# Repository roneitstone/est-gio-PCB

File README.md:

# estagio-PCB
Bioimpedância
Arquivos relacionados ao projeto desenvolvido durante o estágio no laboratório de Instrumentação Biomédica da UFRJ.

--------------------------------------- english version ----------------------------------------------------------

Bioimpedance
Files related to the project developed during the internship at the Biomedical Instrumentation laboratory of UFRJ.

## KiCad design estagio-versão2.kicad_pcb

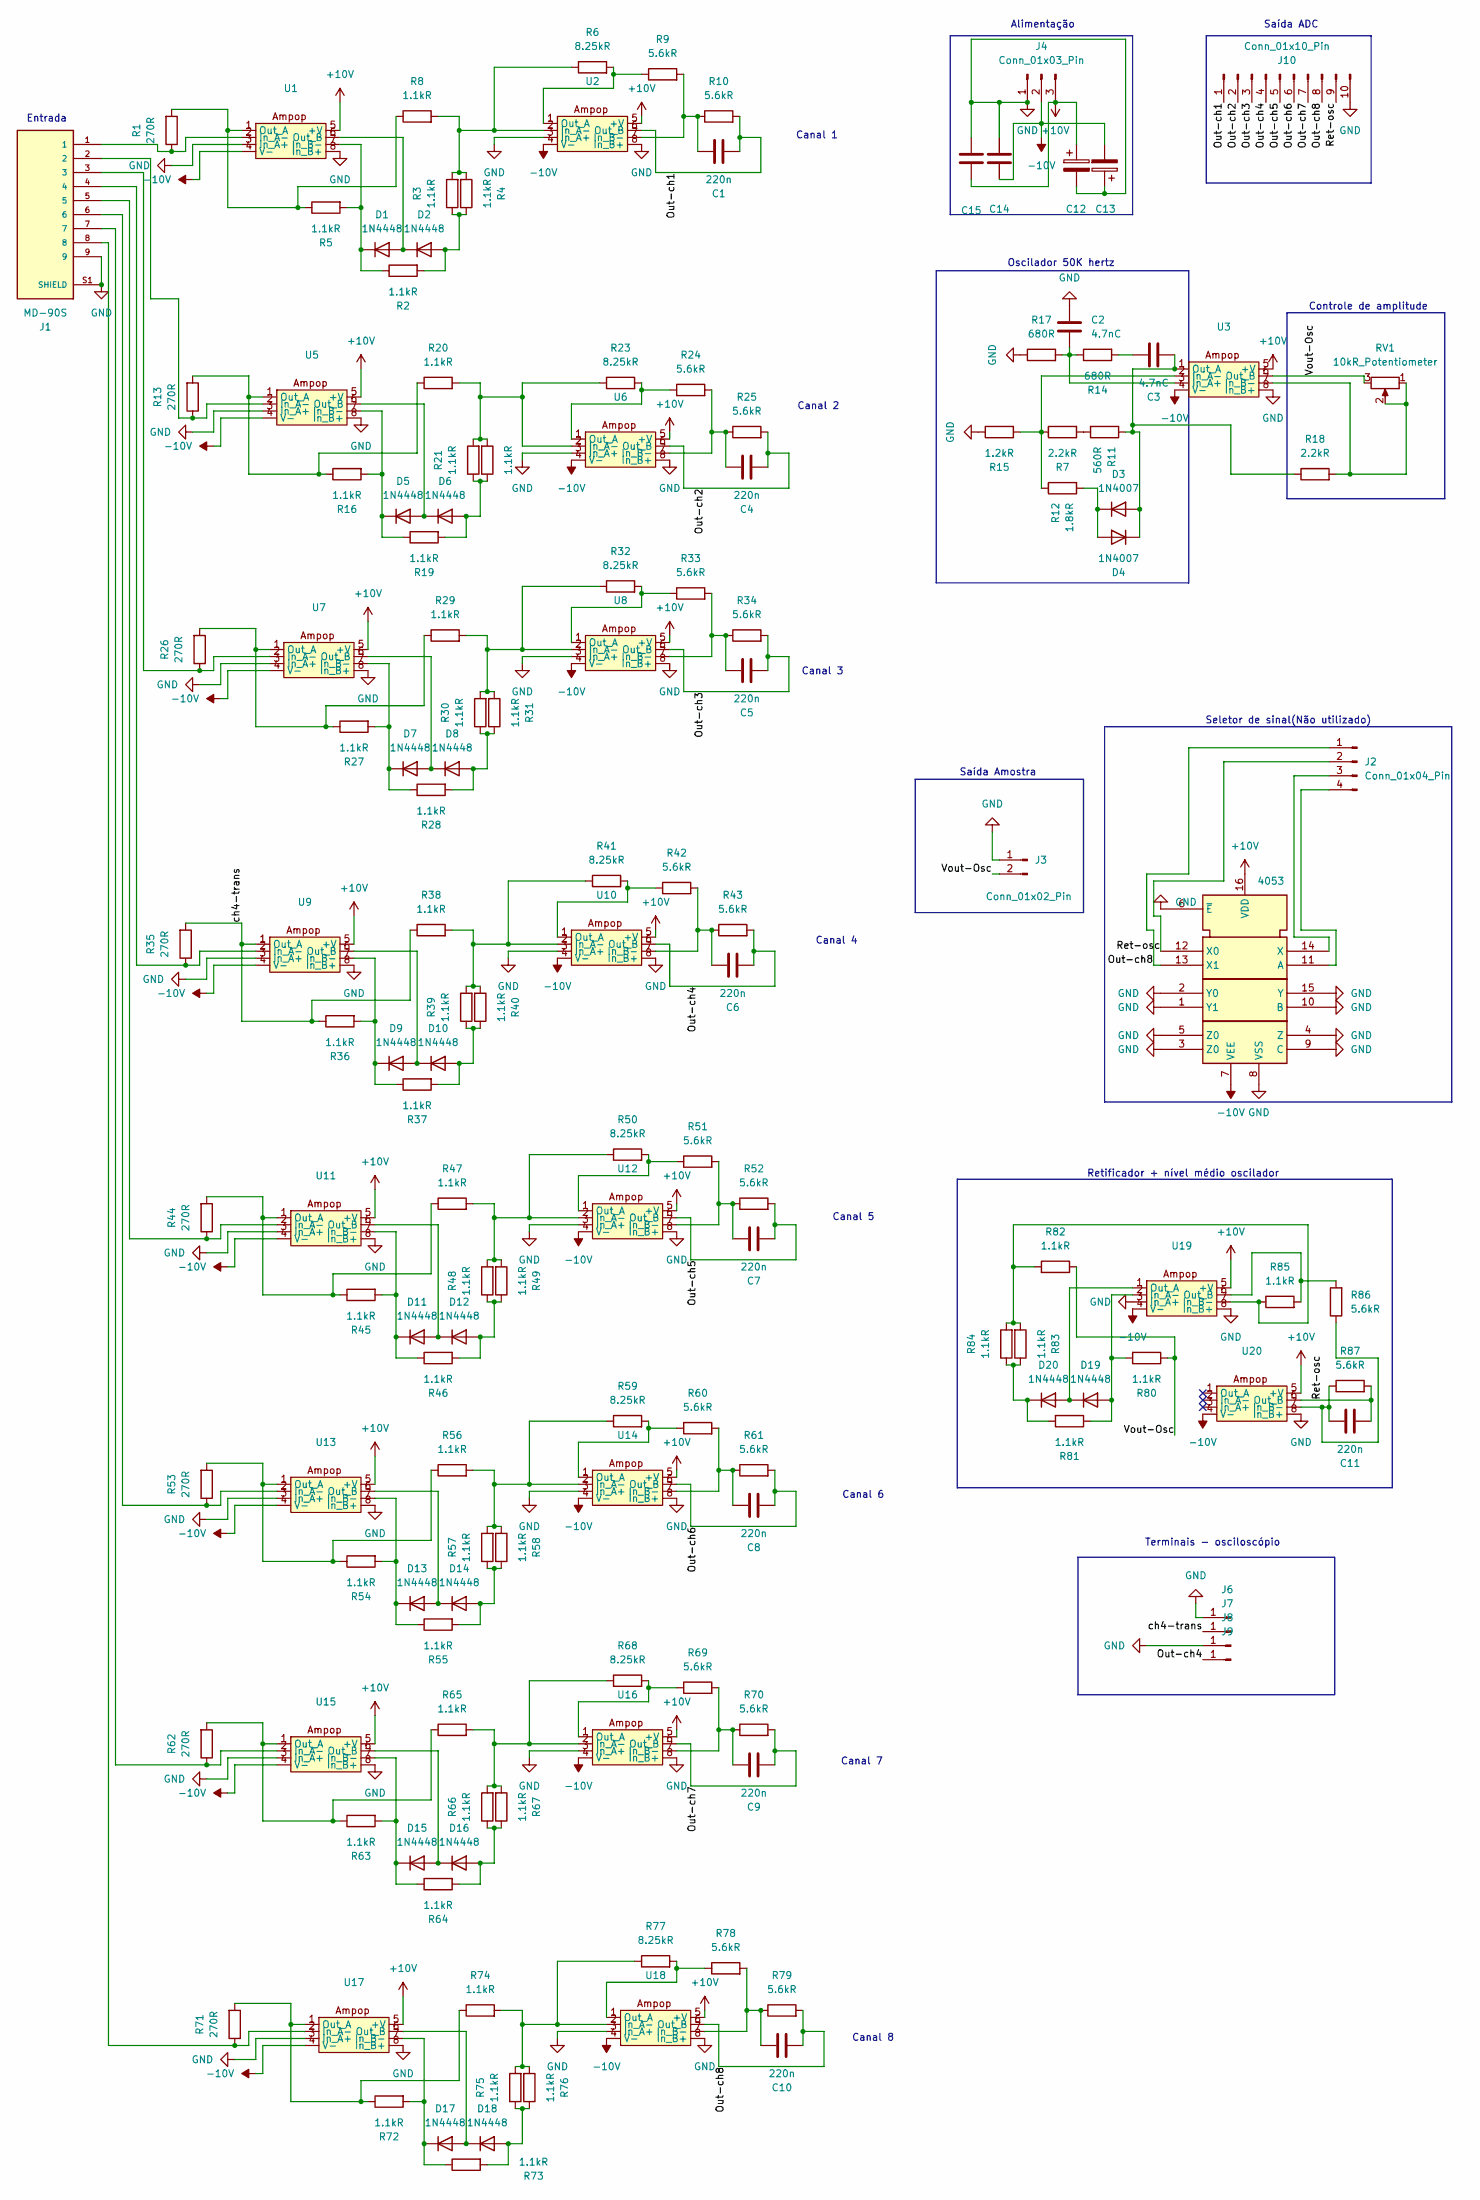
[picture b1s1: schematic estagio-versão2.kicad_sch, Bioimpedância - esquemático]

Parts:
C1, C4, C5, C6, C7, C8, C9, C10, C11: 220n; C_Rect_L7.2mm_W4.5mm_P5.00mm_FKS2_FKP2_MKS2_MKP2
C2, C3: 4.7nC; PinSocket_1x02_P2.54mm_Vertical
C12, C13: 1u; CP_Radial_D5.0mm_P2.50mm
C14, C15: 100n; C_Rect_L7.2mm_W4.5mm_P5.00mm_FKS2_FKP2_MKS2_MKP2
D1, D2, D5, D6, D7, D8, D9, D10, D11, D12, D13, D14, D15, D16, D17, D18, D19, D20: 1N4448; D_DO-35_SOD27_P7.62mm_Horizontal
D3, D4: 1N4007; D_DO-41_SOD81_P10.16mm_Horizontal
J1: MD-90S; CUI_MD-90S; PARTREV 02/18/2022
J2: Conn_01x04_Pin; PinHeader_1x04_P2.54mm_Vertical
J3: Conn_01x02_Pin; PinHeader_1x02_P2.54mm_Vertical
J4: Conn_01x03_Pin; JST_EH_B3B-EH-A_1x03_P2.50mm_Vertical
J6, J7, J8, J9: Conn_01x01_Pin; bullet
J10: Conn_01x10_Pin; PinHeader_1x10_P2.54mm_Vertical
R1, R13, R26, R35, R44, R53, R62, R71: 270R; YAG_MF25_YAG
R2, R3, R4, R5, R8, R16, R19, R20, R21, R22, R27, R28, R29, R30, R31, R36, R37, R38, R39, R40, R45, R46, R47, R48, R49, R54, R55, R56, R57, R58, R63, R64, R65, R66, R67, R72, R73, R74, R75, R76, R80, R81, R82, R83, R84, R85: 1.1kR; RES_TYCO_YR1_TYC
R6, R23, R32, R41, R50, R59, R68, R77: 8.25kR; RES_TYCO_YR1_TYC
R7, R18: 2.2kR; R_Axial_DIN0207_L6.3mm_D2.5mm_P7.62mm_Horizontal
R9, R10, R24, R25, R33, R34, R42, R43, R51, R52, R60, R61, R69, R70, R78, R79, R86, R87: 5.6kR; R_Axial_DIN0207_L6.3mm_D2.5mm_P7.62mm_Horizontal
R11: 560R; R_Axial_DIN0207_L6.3mm_D2.5mm_P7.62mm_Horizontal
R12: 1.8kR; R_Axial_DIN0207_L6.3mm_D2.5mm_P7.62mm_Horizontal
R14, R17: 680R; R_Axial_DIN0207_L6.3mm_D2.5mm_P7.62mm_Horizontal
R15: 1.2kR; R_Axial_DIN0207_L6.3mm_D2.5mm_P7.62mm_Horizontal
RV1: 10kR_Potentiometer; Potentiometer_Bourns_3386C_Horizontal
U1, U2, U3, U5, U6, U7, U8, U9, U10, U11, U12, U13, U14, U15, U16, U17, U18, U19, U20: CONN8_1-2199298-2_TEC
U4: 4053; CONN_A 16-LC-TT_ASM

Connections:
+10V: C12.1, C15.1, J4.3, U1.5 (+V), U2.5 (+V), U3.5 (+V), U4.16 (VDD), U5.5 (+V), U6.5 (+V), U7.5 (+V), U8.5 (+V), U9.5 (+V), U10.5 (+V), U11.5 (+V), U12.5 (+V), U13.5 (+V), U14.5 (+V), U15.5 (+V), U16.5 (+V), U17.5 (+V), U18.5 (+V), U19.5 (+V), U20.5 (+V)
-10V: C13.2, C14.1, J4.2, U1.4 (V-), U2.4 (V-), U3.4 (V-), U4.7 (VEE), U5.4 (V-), U6.4 (V-), U7.4 (V-), U8.4 (V-), U9.4 (V-), U10.4 (V-), U11.4 (V-), U12.4 (V-), U13.4 (V-), U14.4 (V-), U15.4 (V-), U16.4 (V-), U17.4 (V-), U18.4 (V-), U19.4 (V-), U20.4 (V-)
/Out-ch1: C1.2, J10.1, R10.2, U2.6 (Out_B)
/Out-ch2: C4.2, J10.2, R25.2, U6.6 (Out_B)
/Out-ch3: C5.2, J10.3, R34.2, U8.6 (Out_B)
/Out-ch4: C6.2, J9.1, J10.4, R43.2, U10.6 (Out_B)
/Out-ch5: C7.2, J10.5, R52.2, U12.6 (Out_B)
/Out-ch6: C8.2, J10.6, R61.2, U14.6 (Out_B)
/Out-ch7: C9.2, J10.7, R70.2, U16.6 (Out_B)
/Out-ch8: C10.2, J2.1, J10.8, R79.2, U4.13 (X1), U18.6 (Out_B)
/Ret-osc: C11.2, J2.2, J10.9, R87.2, U4.12 (X0), U20.6 (Out_B)
/Vout-Osc: J3.2, R80.1, R82.1, RV1.3, U3.6 (Out_B)
/ch4-trans: J7.1, R35.2, R36.1, R38.1, U9.1 (Out_A)
GND: C2.2, C12.2, C13.1, C14.2, C15.2, J1.9, J1.S1 (SHIELD), J3.1, J4.1, J6.1, J8.1, J10.10, R15.1, R17.1, U1.3 (In_A+), U1.8 (In_B+), U2.3 (In_A+), U2.8 (In_B+), U3.8 (In_B+), U4.1 (Y1), U4.2 (Y0), U4.3 (Z0), U4.4 (Z), U4.5 (Z0), U4.6 (~E), U4.8 (VSS), U4.9 (C), U4.10 (B), U4.15 (Y), U5.3 (In_A+), U5.8 (In_B+), U6.3 (In_A+), U6.8 (In_B+), U7.3 (In_A+), U7.8 (In_B+), U8.3 (In_A+), U8.8 (In_B+), U9.3 (In_A+), U9.8 (In_B+), U10.3 (In_A+), U10.8 (In_B+), U11.3 (In_A+), U11.8 (In_B+), U12.3 (In_A+), U12.8 (In_B+), U13.3 (In_A+), U13.8 (In_B+), U14.3 (In_A+), U14.8 (In_B+), U15.3 (In_A+), U15.8 (In_B+), U16.3 (In_A+), U16.8 (In_B+), U17.3 (In_A+), U17.8 (In_B+), U18.3 (In_A+), U18.8 (In_B+), U19.3 (In_A+), U19.8 (In_B+), U20.8 (In_B+)
unnamed: C3.1, R14.2
unnamed: D1.2 (A), D2.1 (K), U1.6 (Out_B)
unnamed: D1.1 (K), R2.1, R5.2, U1.7 (In_B-)
unnamed: D2.2 (A), R2.2, R3.1, R4.1
unnamed: C3.2, D3.2 (A), D4.1 (K), R11.1, R18.1, U3.1 (Out_A)
unnamed: D3.1 (K), D4.2 (A), R12.2
unnamed: D5.2 (A), D6.1 (K), U5.6 (Out_B)
unnamed: D5.1 (K), R16.2, R19.1, U5.7 (In_B-)
unnamed: D6.2 (A), R19.2, R21.1, R22.1
unnamed: D7.2 (A), D8.1 (K), U7.6 (Out_B)
unnamed: D7.1 (K), R27.2, R28.1, U7.7 (In_B-)
unnamed: D8.2 (A), R28.2, R30.1, R31.1
unnamed: D9.1 (K), R36.2, R37.1, U9.7 (In_B-)
unnamed: D10.2 (A), R37.2, R39.1, R40.1
unnamed: D9.2 (A), D10.1 (K), U9.6 (Out_B)
unnamed: D11.2 (A), D12.1 (K), U11.6 (Out_B)
unnamed: D11.1 (K), R45.2, R46.1, U11.7 (In_B-)
unnamed: D12.2 (A), R46.2, R48.1, R49.1
unnamed: D13.2 (A), D14.1 (K), U13.6 (Out_B)
unnamed: D13.1 (K), R54.2, R55.1, U13.7 (In_B-)
unnamed: D14.2 (A), R55.2, R57.1, R58.1
unnamed: D15.2 (A), D16.1 (K), U15.6 (Out_B)
unnamed: D15.1 (K), R63.2, R64.1, U15.7 (In_B-)
unnamed: D16.2 (A), R64.2, R66.1, R67.1
unnamed: D17.2 (A), D18.1 (K), U17.6 (Out_B)
unnamed: D17.1 (K), R72.2, R73.1, U17.7 (In_B-)
unnamed: D18.2 (A), R73.2, R75.1, R76.1
unnamed: D19.2 (A), R80.2, R81.1, U19.2 (In_A-)
unnamed: D19.1 (K), D20.2 (A), U19.1 (Out_A)
unnamed: D20.1 (K), R81.2, R83.1, R84.1
unnamed: J2.3, U4.14 (X)
unnamed: J2.4, U4.11 (A)
unnamed: R7.2, R11.2
unnamed: J1.1, R1.1, U1.2 (In_A-)
unnamed: R1.2, R5.1, R8.1, U1.1 (Out_A)
unnamed: R3.2, R4.2, R6.1, R8.2, U2.2 (In_A-)
unnamed: C1.1, R9.2, R10.1, U2.7 (In_B-)
unnamed: R6.2, R9.1, U2.1 (Out_A)
unnamed: C2.1, R14.1, R17.2, U3.3 (In_A+)
unnamed: R7.1, R12.1, R15.2, U3.2 (In_A-)
unnamed: R18.2, RV1.1, RV1.2, U3.7 (In_B-)
unnamed: J1.2, R13.1, U5.2 (In_A-)
unnamed: R13.2, R16.1, R20.1, U5.1 (Out_A)
unnamed: R20.2, R21.2, R22.2, R23.1, U6.2 (In_A-)
unnamed: C4.1, R24.2, R25.1, U6.7 (In_B-)
unnamed: R23.2, R24.1, U6.1 (Out_A)
unnamed: J1.3, R26.1, U7.2 (In_A-)
unnamed: R26.2, R27.1, R29.1, U7.1 (Out_A)
unnamed: R29.2, R30.2, R31.2, R32.1, U8.2 (In_A-)
unnamed: C5.1, R33.2, R34.1, U8.7 (In_B-)
unnamed: R32.2, R33.1, U8.1 (Out_A)
unnamed: J1.4, R35.1, U9.2 (In_A-)
unnamed: R38.2, R39.2, R40.2, R41.1, U10.2 (In_A-)
unnamed: C6.1, R42.2, R43.1, U10.7 (In_B-)
unnamed: R41.2, R42.1, U10.1 (Out_A)
unnamed: J1.5, R44.1, U11.2 (In_A-)
unnamed: R44.2, R45.1, R47.1, U11.1 (Out_A)
unnamed: R47.2, R48.2, R49.2, R50.1, U12.2 (In_A-)
unnamed: C7.1, R51.2, R52.1, U12.7 (In_B-)
unnamed: R50.2, R51.1, U12.1 (Out_A)
unnamed: J1.6, R53.1, U13.2 (In_A-)
unnamed: R53.2, R54.1, R56.1, U13.1 (Out_A)
unnamed: R56.2, R57.2, R58.2, R59.1, U14.2 (In_A-)
unnamed: C8.1, R60.2, R61.1, U14.7 (In_B-)
unnamed: R59.2, R60.1, U14.1 (Out_A)
unnamed: J1.7, R62.1, U15.2 (In_A-)
unnamed: R62.2, R63.1, R65.1, U15.1 (Out_A)
unnamed: R65.2, R66.2, R67.2, R68.1, U16.2 (In_A-)
unnamed: C9.1, R69.2, R70.1, U16.7 (In_B-)
unnamed: R68.2, R69.1, U16.1 (Out_A)
unnamed: J1.8, R71.1, U17.2 (In_A-)
unnamed: R71.2, R72.1, R74.1, U17.1 (Out_A)
unnamed: R74.2, R75.2, R76.2, R77.1, U18.2 (In_A-)
unnamed: C10.1, R78.2, R79.1, U18.7 (In_B-)
unnamed: R77.2, R78.1, U18.1 (Out_A)
unnamed: R82.2, R83.2, R84.2, R85.1, U19.7 (In_B-)
unnamed: R85.2, R86.2, U19.6 (Out_B)
unnamed: C11.1, R86.1, R87.1, U20.7 (In_B-)

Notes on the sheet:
Canal 4
Saída ADC
Canal 5
Saída Amostra
Canal 7
Alimentação
Canal 2
Terminais - osciloscópio
Entrada
Controle de amplitude
Canal 6
Canal 8
Canal 3
Seletor de sinal(Não utilizado)
Retificador + nível médio oscilador
Canal 1
Oscilador 50K hertz

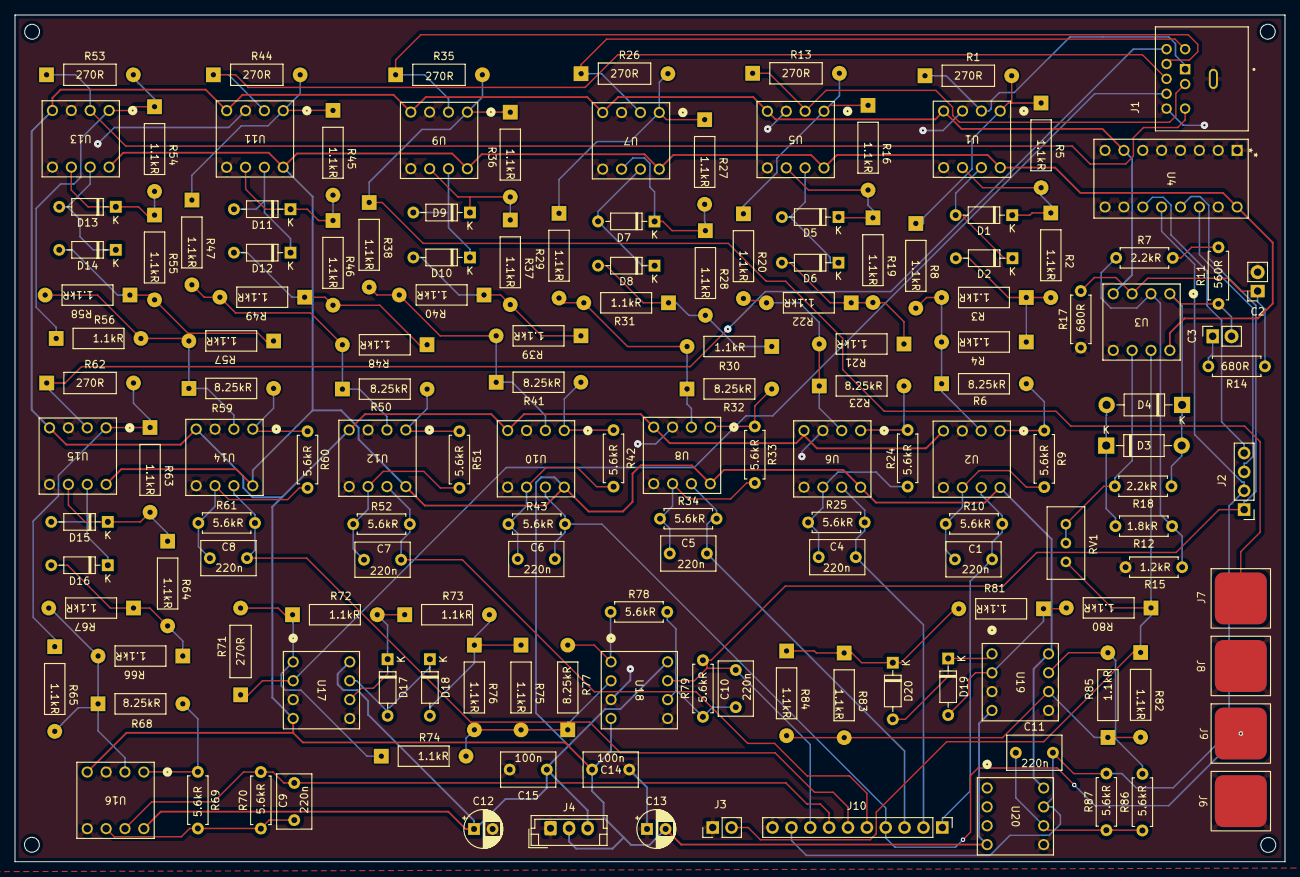
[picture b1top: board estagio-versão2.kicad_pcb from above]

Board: 4 copper layers, 171.0 x 114.0 mm, 152 parts (0 on the bottom side), 92 nets.

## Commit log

2025-02-14 Add files related to my trainee project.
2025-11-08 Update README.md
    English version added.
